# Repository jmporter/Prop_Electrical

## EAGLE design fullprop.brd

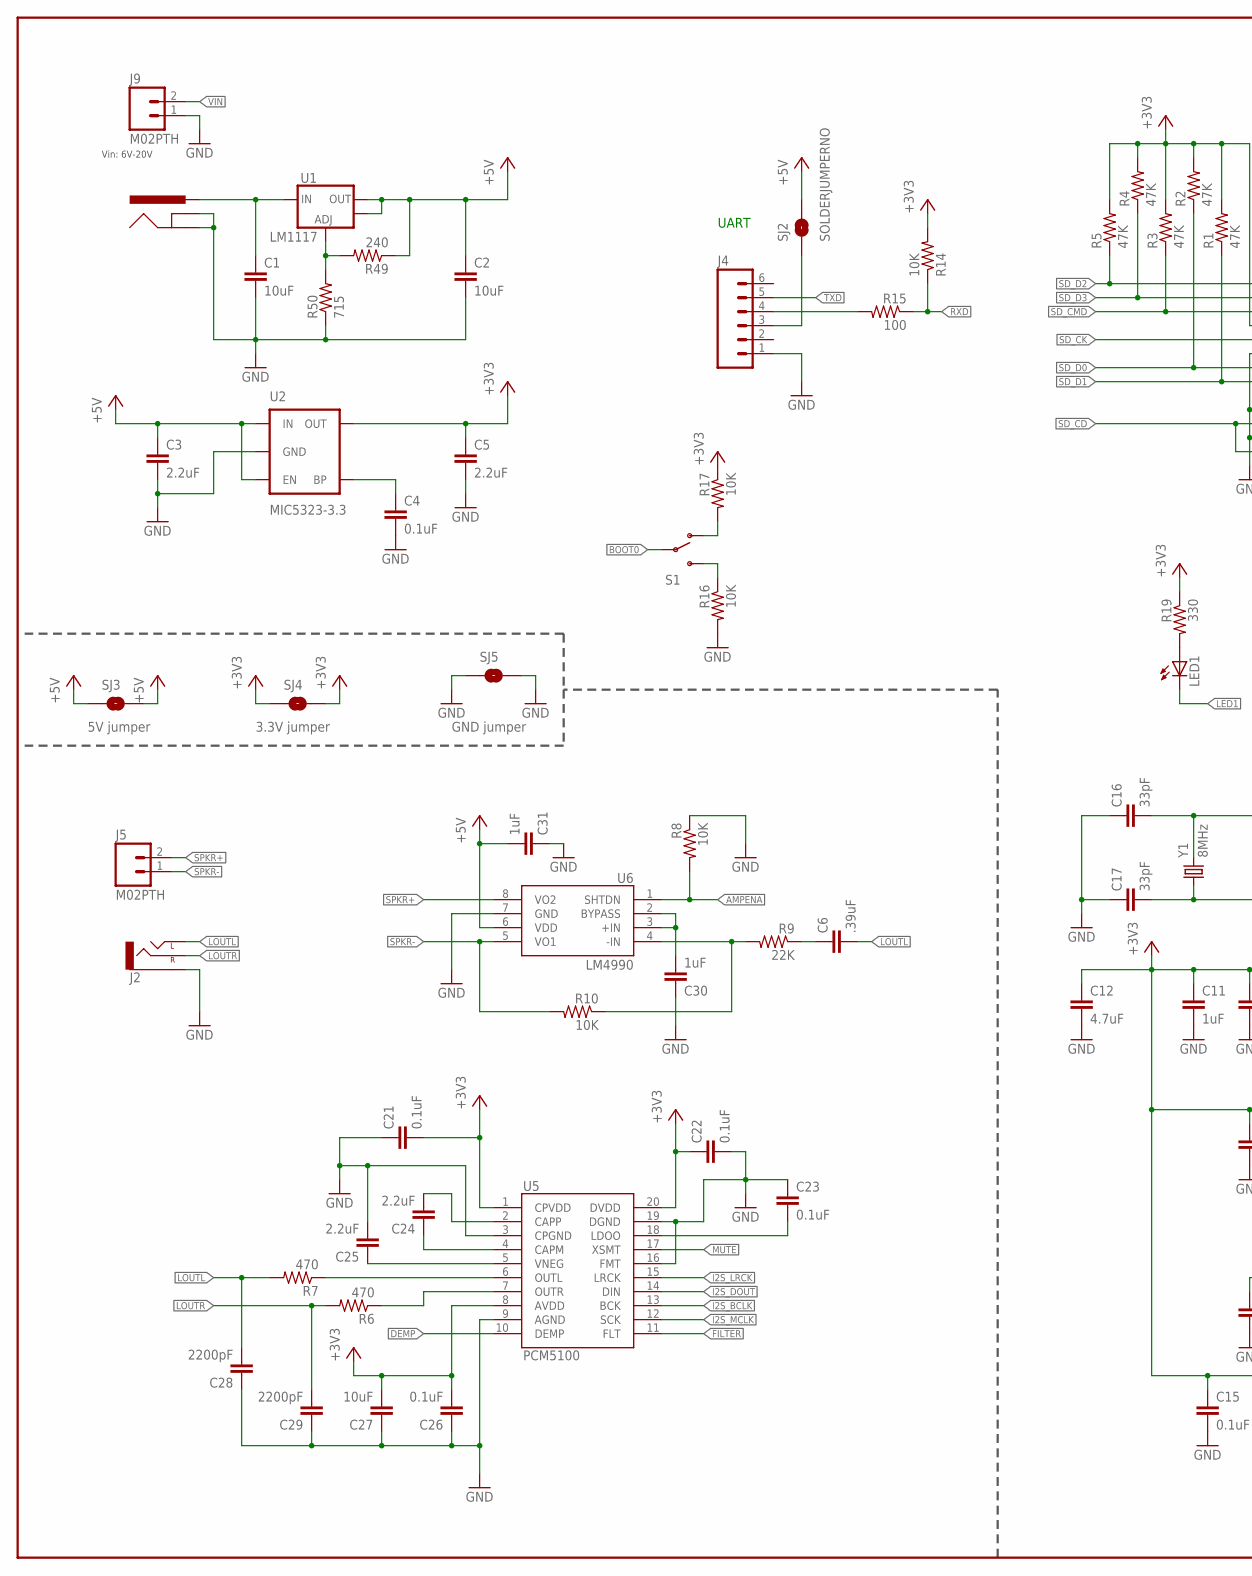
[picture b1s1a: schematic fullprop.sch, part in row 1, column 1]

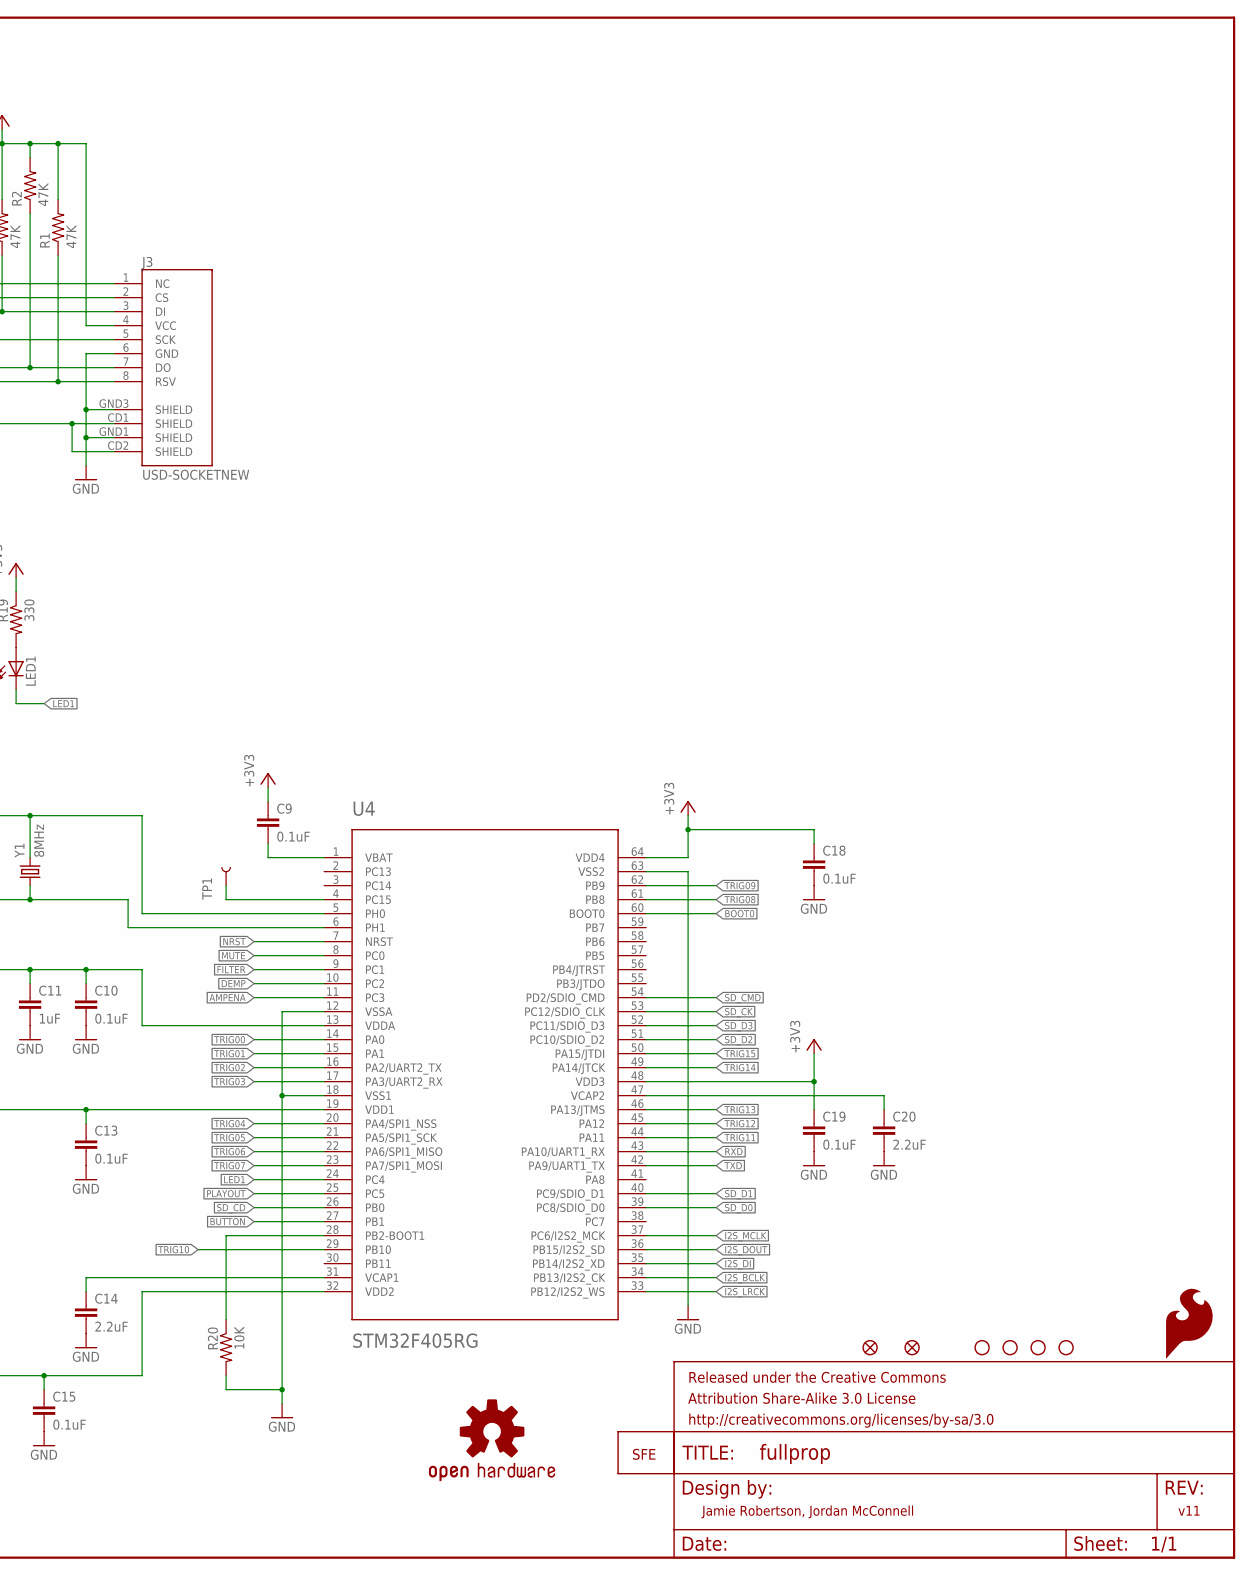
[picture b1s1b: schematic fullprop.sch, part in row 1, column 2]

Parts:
C1: 10uF; 1210
C2: 10uF; 0805
C3, C5: 2.2uF; 0805
C4, C9, C10, C13, C15, C18, C19, C21, C22, C23, C26: 0.1uF; 0603-CAP
C6: .39uF; 0603-CAP
C11, C30, C31: 1uF; 0603-CAP
C12: 4.7uF; 0603-CAP
C14, C20, C24, C25: 2.2uF; 0603-CAP
C16, C17: 33pF; 0603-CAP
C27: 10uF; 0603-CAP
C28, C29: 2200pF; 0603-CAP
FID1, FID2: FIDUCIAL1X2; FIDUCIAL-1X2
FRAME2: FRAME-LEDGER; CREATIVE_COMMONS
J1: 5.5x2.1mm Barrel; POWER_JACK_SMD_OVERPASTE_REDBOARD_0603
J2: AUDIO-JACKSMD2; AUDIO-JACK-3.5MM-SMD
J3: USD-SOCKETNEW; MICRO-SD-SOCKET-PP
J4: M06SIP; 1X06
J5, J9: M02PTH; 1X02
LED1: LED0603; LED-0603
LOGO1: OSHW-LOGOL; OSHW-LOGO-L
LOGO2: LOGO-SFENEW; SFE-NEW-WEBLOGO
LOGO4: SFE_LOGO_FLAME.2_INCH; SFE_LOGO_FLAME_.2
R1, R2, R3, R4, R5: 47K; 0603-RES
R6, R7: 470; 0603-RES
R8, R10, R14, R16, R17, R20: 10K; 0603-RES
R9: 22K; 0603-RES
R15: 100; 0603-RES
R19: 330; 0603-RES
R49: 240; 0603-RES
R50: 715; 0603-RES
S1: SWITCH-SPDT-SMD-A; SWITCH-SPST-SMD-A
SJ2: SOLDERJUMPERNO; SJ_2S-NO
SJ3, SJ4, SJ5: SOLDERJUMPERTRACE; SJ_2S-TRACE
STANDOFF1, STANDOFF2, STANDOFF3, STANDOFF4: STAND-OFF
TP1: TEST-POINTTP_15TH_THRU; TP_15TH
U1: V_REG_LM1117SOT223; SOT223
U2: MIC5323-3.3; SOT23-5
U4: STM32F405RG; TQFP64
U5: PCM5100; PW_R-PDSO-G20
U6: LM4990; S-PDSO-G08
Y1: 8MHz; HC49UP

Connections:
+5V: C2.1, C3.1, C31.2, R49.1, SJ2.2, SJ3.1, SJ3.2, U1.2 (OUT), U1.4 (OUT), U2.1 (IN), U2.3 (EN), U6.6 (VDD)
AMPENA: R8.2, U4.11 (PC3), U6.1 (SHTDN)
BOOT0: S1.2, U4.60 (BOOT0)
BUTTON: U4.27 (PB1)
DEMP: U4.10 (PC2), U5.10 (DEMP)
FILTER: U4.9 (PC1), U5.11 (FLT)
GND: C1.2, C2.2, C3.2, C4.2, C5.2, C10.2, C11.2, C12.2, C13.2, C14.2, C15.2, C16.1, C17.1, C18.2, C19.2, C20.2, C21.1, C22.2, C23.1, C25.2, C26.1, C27.1, C28.1, C29.1, C30.1, C31.1, J1.GND (GNDBREAK), J1.P$4 (GND), J2.SLEEVE, J3.6 (GND), J3.GND1 (SHIELD), J3.GND3 (SHIELD), J4.1, J9.1, R8.1, R16.2, R20.2, R50.1, SJ5.1, SJ5.2, U2.2 (GND), U4.12 (VSSA), U4.18 (VSS1), U4.63 (VSS2), U5.3 (CPGND), U5.9 (AGND), U5.16 (FMT), U5.19 (DGND), U6.7 (GND)
I2S_BCLK: U4.34 (PB13/I2S2_CK), U5.13 (BCK)
I2S_DI: U4.35 (PB14/I2S2_XD)
I2S_DOUT: U4.36 (PB15/I2S2_SD), U5.14 (DIN)
I2S_LRCK: U4.33 (PB12/I2S2_WS), U5.15 (LRCK)
I2S_MCLK: U4.37 (PC6/I2S2_MCK), U5.12 (SCK)
LED1: LED1.C, U4.24 (PC4)
LOUTL: C6.2, C28.2, J2.TIP (LEFT), R7.2
LOUTR: C29.2, J2.RING (RIGHT), R6.2
MUTE: U4.8 (PC0), U5.17 (XSMT)
unnamed: C4.1, U2.4 (BP)
unnamed: C9.2, U4.1 (VBAT)
unnamed: C14.1, U4.31 (VCAP1)
unnamed: C16.2, U4.5 (PH0), Y1.2
unnamed: C17.2, U4.6 (PH1), Y1.1
unnamed: R16.1, S1.3 (S)
unnamed: C20.1, U4.47 (VCAP2)
unnamed: J4.4, R15.2
unnamed: R17.2, S1.1 (O)
unnamed: LED1.A, R19.2
unnamed: R20.1, U4.28 (PB2-BOOT1)
unnamed: R49.2, R50.2, U1.1 (ADJ)
unnamed: C23.2, U5.18 (LDOO)
unnamed: R6.1, U5.7 (OUTR)
unnamed: C24.2, U5.2 (CAPP)
unnamed: C24.1, U5.4 (CAPM)
unnamed: C25.1, U5.5 (VNEG)
unnamed: R7.1, U5.6 (OUTL)
unnamed: C30.2, U6.2 (BYPASS), U6.3 (+IN)
unnamed: C6.1, R9.1
unnamed: TP1.P$1, U4.4 (PC15)
unnamed: R9.2, R10.1, U6.4 (-IN)
unnamed: J4.3, SJ2.1
NRST: U4.7 (NRST)
PLAYOUT: U4.25 (PC5)
RXD: R14.1, R15.1, U4.43 (PA10/UART1_RX)
SD_CD: J3.CD1 (SHIELD), J3.CD2 (SHIELD), U4.26 (PB0)
SD_CK: J3.5 (SCK), U4.53 (PC12/SDIO_CLK)
SD_CMD: J3.3 (DI), R3.1, U4.54 (PD2/SDIO_CMD)
SD_D0: J3.7 (DO), R2.1, U4.39 (PC8/SDIO_D0)
SD_D1: J3.8 (RSV), R1.1, U4.40 (PC9/SDIO_D1)
SD_D2: J3.1 (NC), R5.1, U4.51 (PC10/SDIO_D2)
SD_D3: J3.2 (CS), R4.1, U4.52 (PC11/SDIO_D3)
SPKR+: J5.2, U6.8 (VO2)
SPKR-: J5.1, R10.2, U6.5 (VO1)
TRIG00: U4.14 (PA0)
TRIG01: U4.15 (PA1)
TRIG02: U4.16 (PA2/UART2_TX)
TRIG03: U4.17 (PA3/UART2_RX)
TRIG04: U4.20 (PA4/SPI1_NSS)
TRIG05: U4.21 (PA5/SPI1_SCK)
TRIG06: U4.22 (PA6/SPI1_MISO)
TRIG07: U4.23 (PA7/SPI1_MOSI)
TRIG08: U4.61 (PB8)
TRIG09: U4.62 (PB9)
TRIG10: U4.29 (PB10)
TRIG11: U4.44 (PA11)
TRIG12: U4.45 (PA12)
TRIG13: U4.46 (PA13/JTMS)
TRIG14: U4.49 (PA14/JTCK)
TRIG15: U4.50 (PA15/JTDI)
TXD: J4.5, U4.42 (PA9/UART1_TX)
VCC: C5.1, C9.1, C10.1, C11.1, C12.1, C13.1, C15.1, C18.1, C19.1, C21.2, C22.1, C26.2, C27.2, J3.4 (VCC), R1.2, R2.2, R3.2, R4.2, R5.2, R14.2, R17.1, R19.1, SJ4.1, SJ4.2, U2.5 (OUT), U4.13 (VDDA), U4.19 (VDD1), U4.32 (VDD2), U4.48 (VDD3), U4.64 (VDD4), U5.1 (CPVDD), U5.8 (AVDD), U5.20 (DVDD)
VIN: C1.1, J1.VIN0 (PWR), J9.2, U1.3 (IN)

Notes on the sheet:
Jamie Robertson, Jordan McConnell
5V jumper
3.3V jumper
GND jumper
LM1117
Vin: 6V-20V
v11
UART

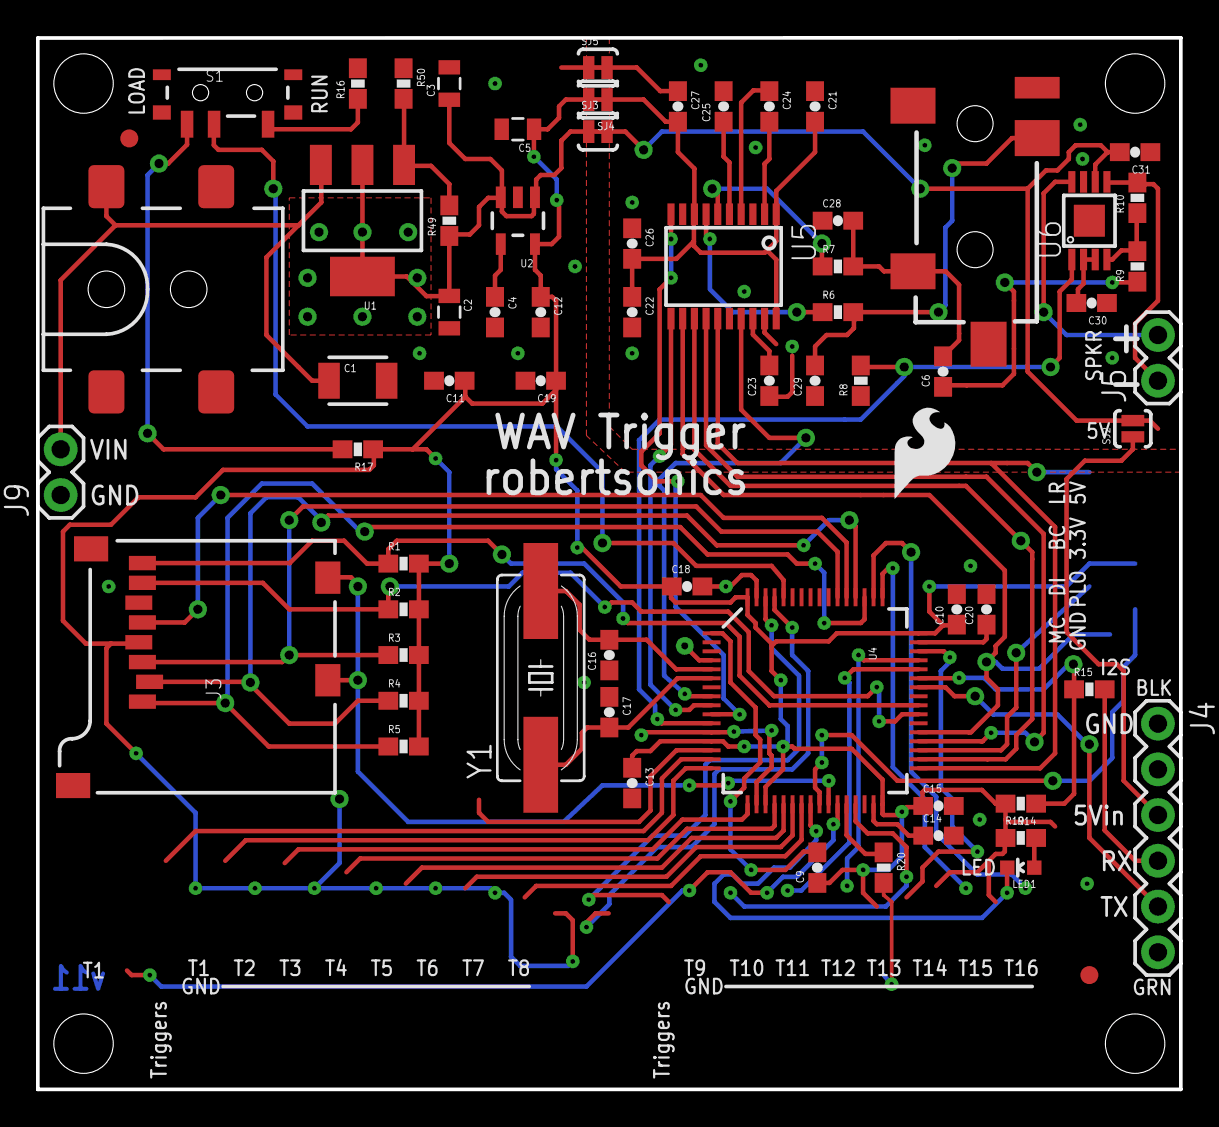
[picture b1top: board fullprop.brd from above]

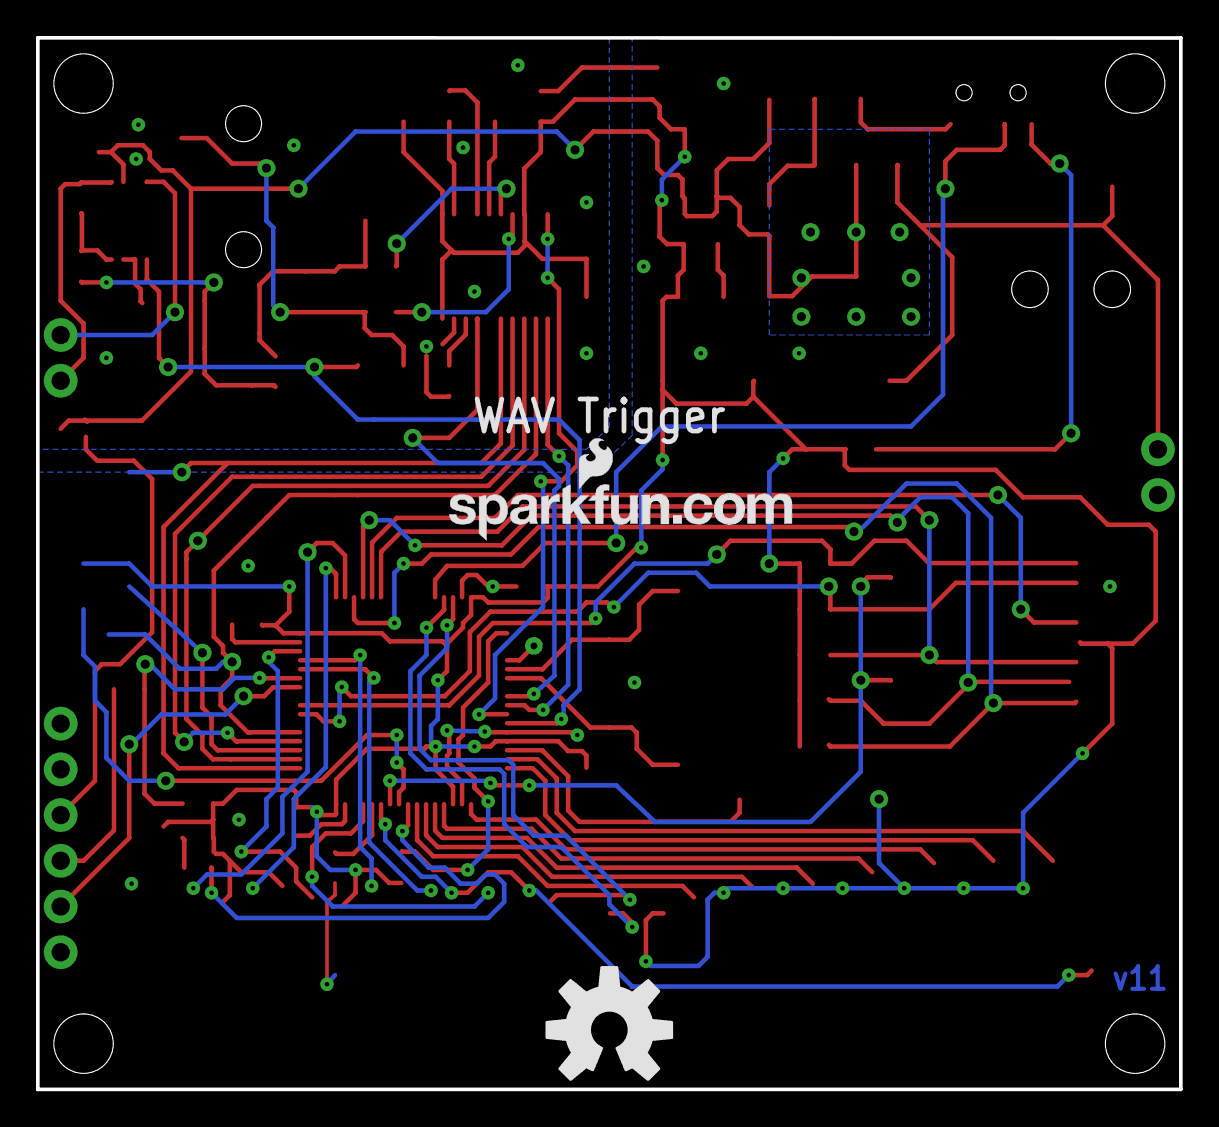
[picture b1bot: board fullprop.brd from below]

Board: 2 copper layers, 63.5 x 58.4 mm, 76 parts (2 on the bottom side), 50 nets.

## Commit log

2017-04-06 Wave Trigger Teardown

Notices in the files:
parts and their libraries:
SparkFun-Connectors: Licensing: CC v3.0 Share-Alike You are welcome to use this library for commercial purposes.
SparkFun-Aesthetics: Released under the Creative Commons Attribution Share-Alike 3.0 License
SparkFun-Aesthetics: http://creativecommons.org/licenses/by-sa/3.0
